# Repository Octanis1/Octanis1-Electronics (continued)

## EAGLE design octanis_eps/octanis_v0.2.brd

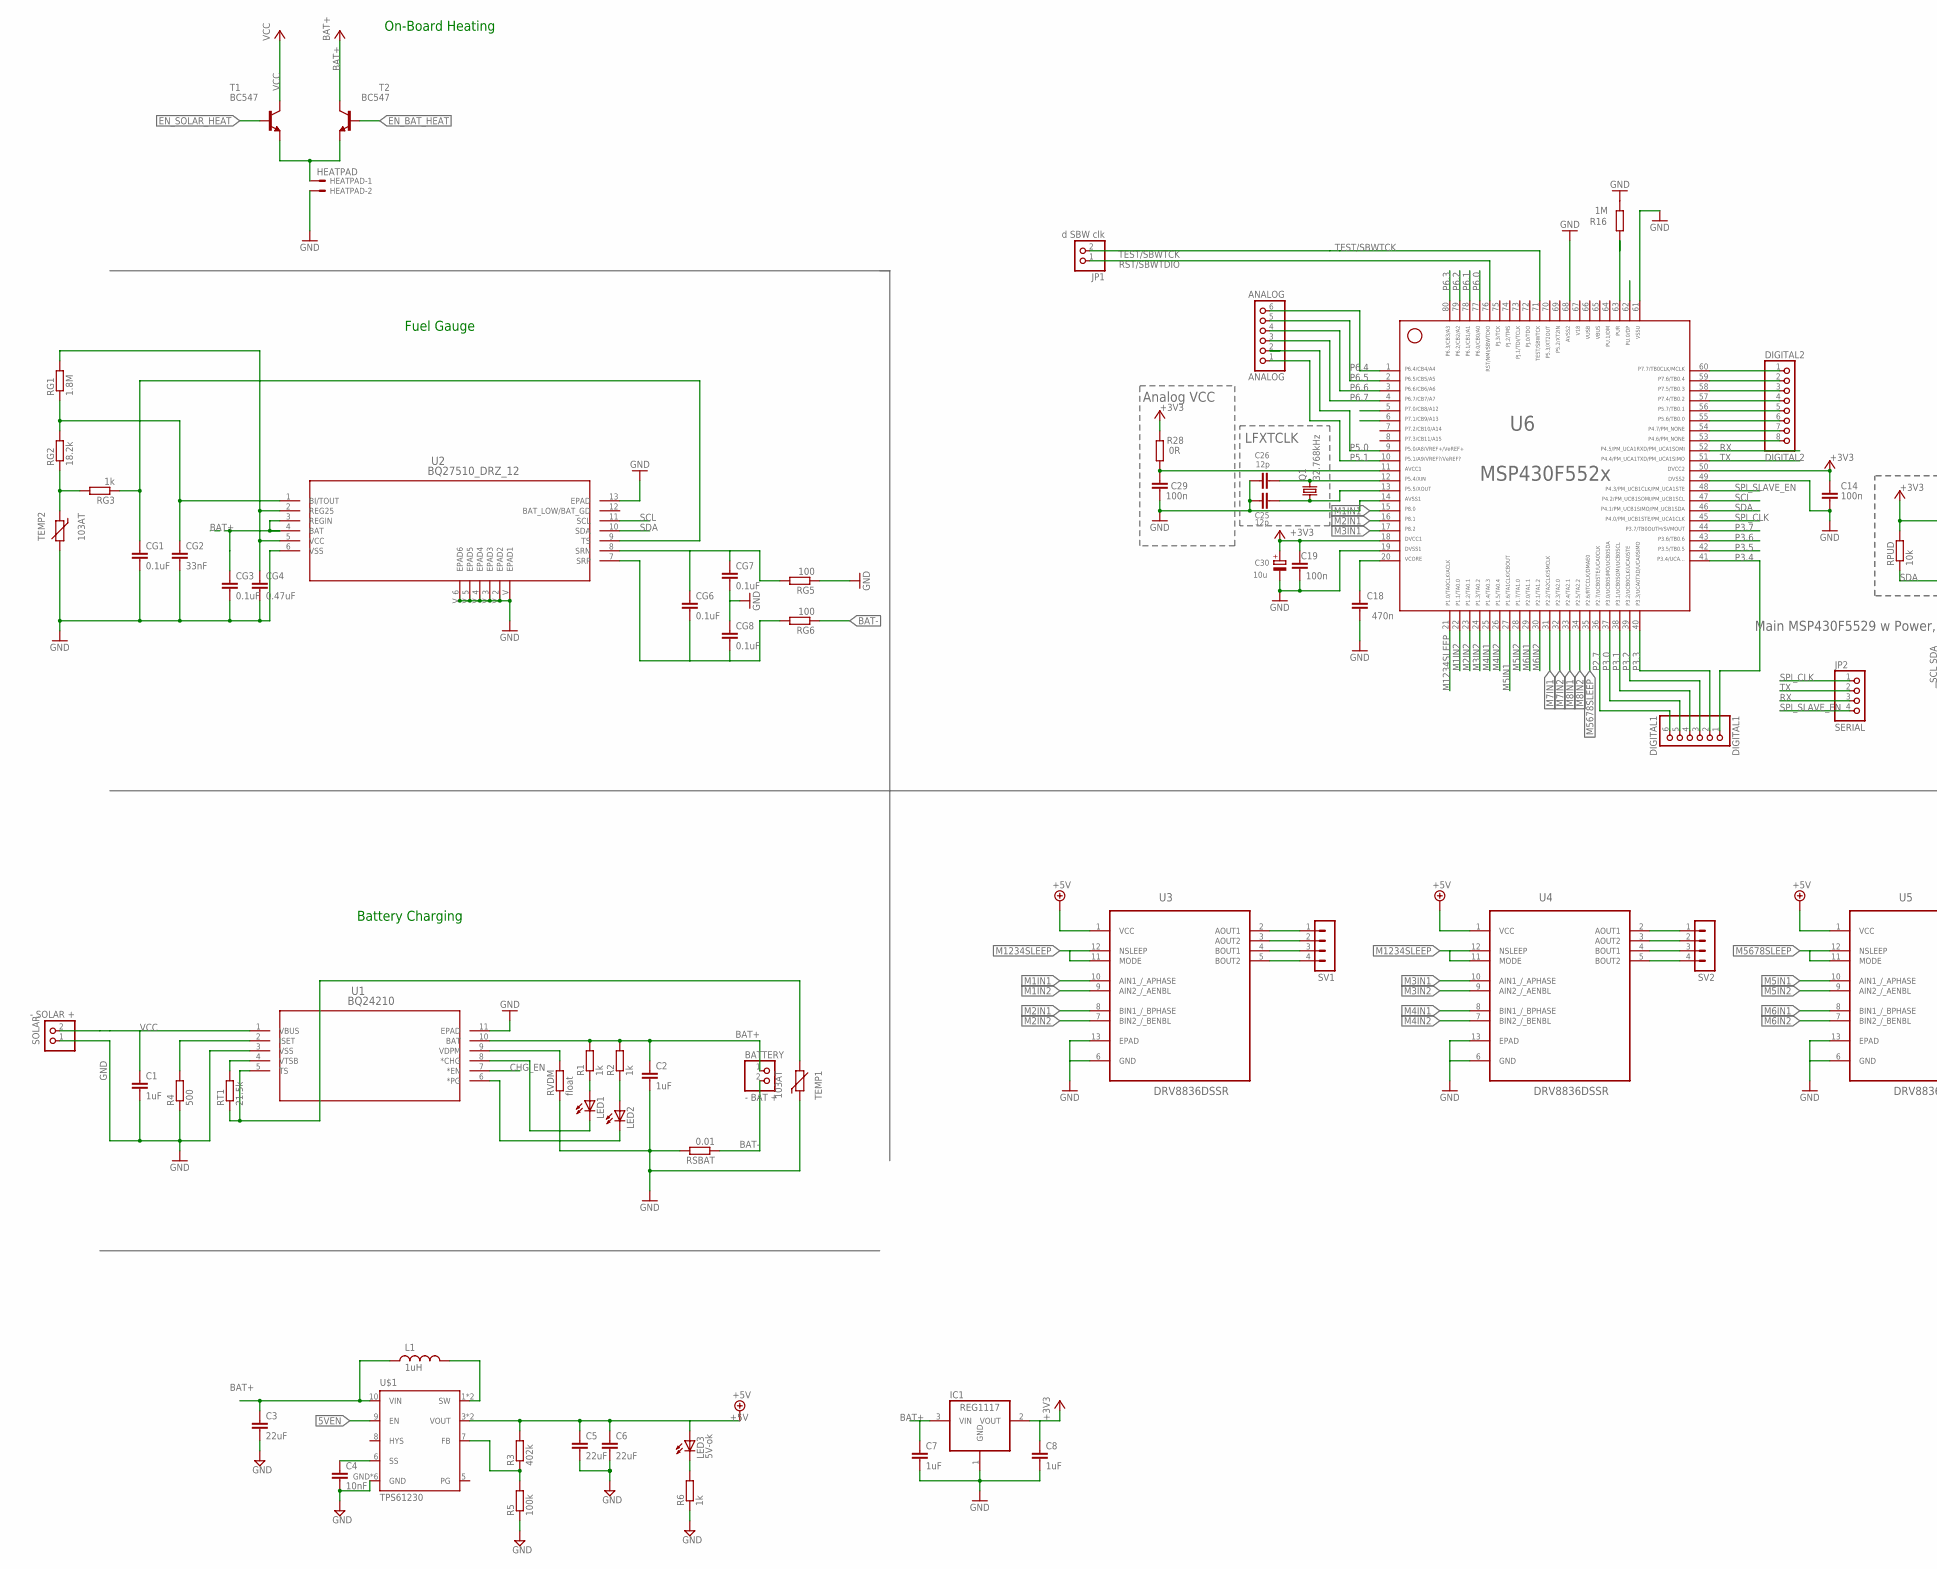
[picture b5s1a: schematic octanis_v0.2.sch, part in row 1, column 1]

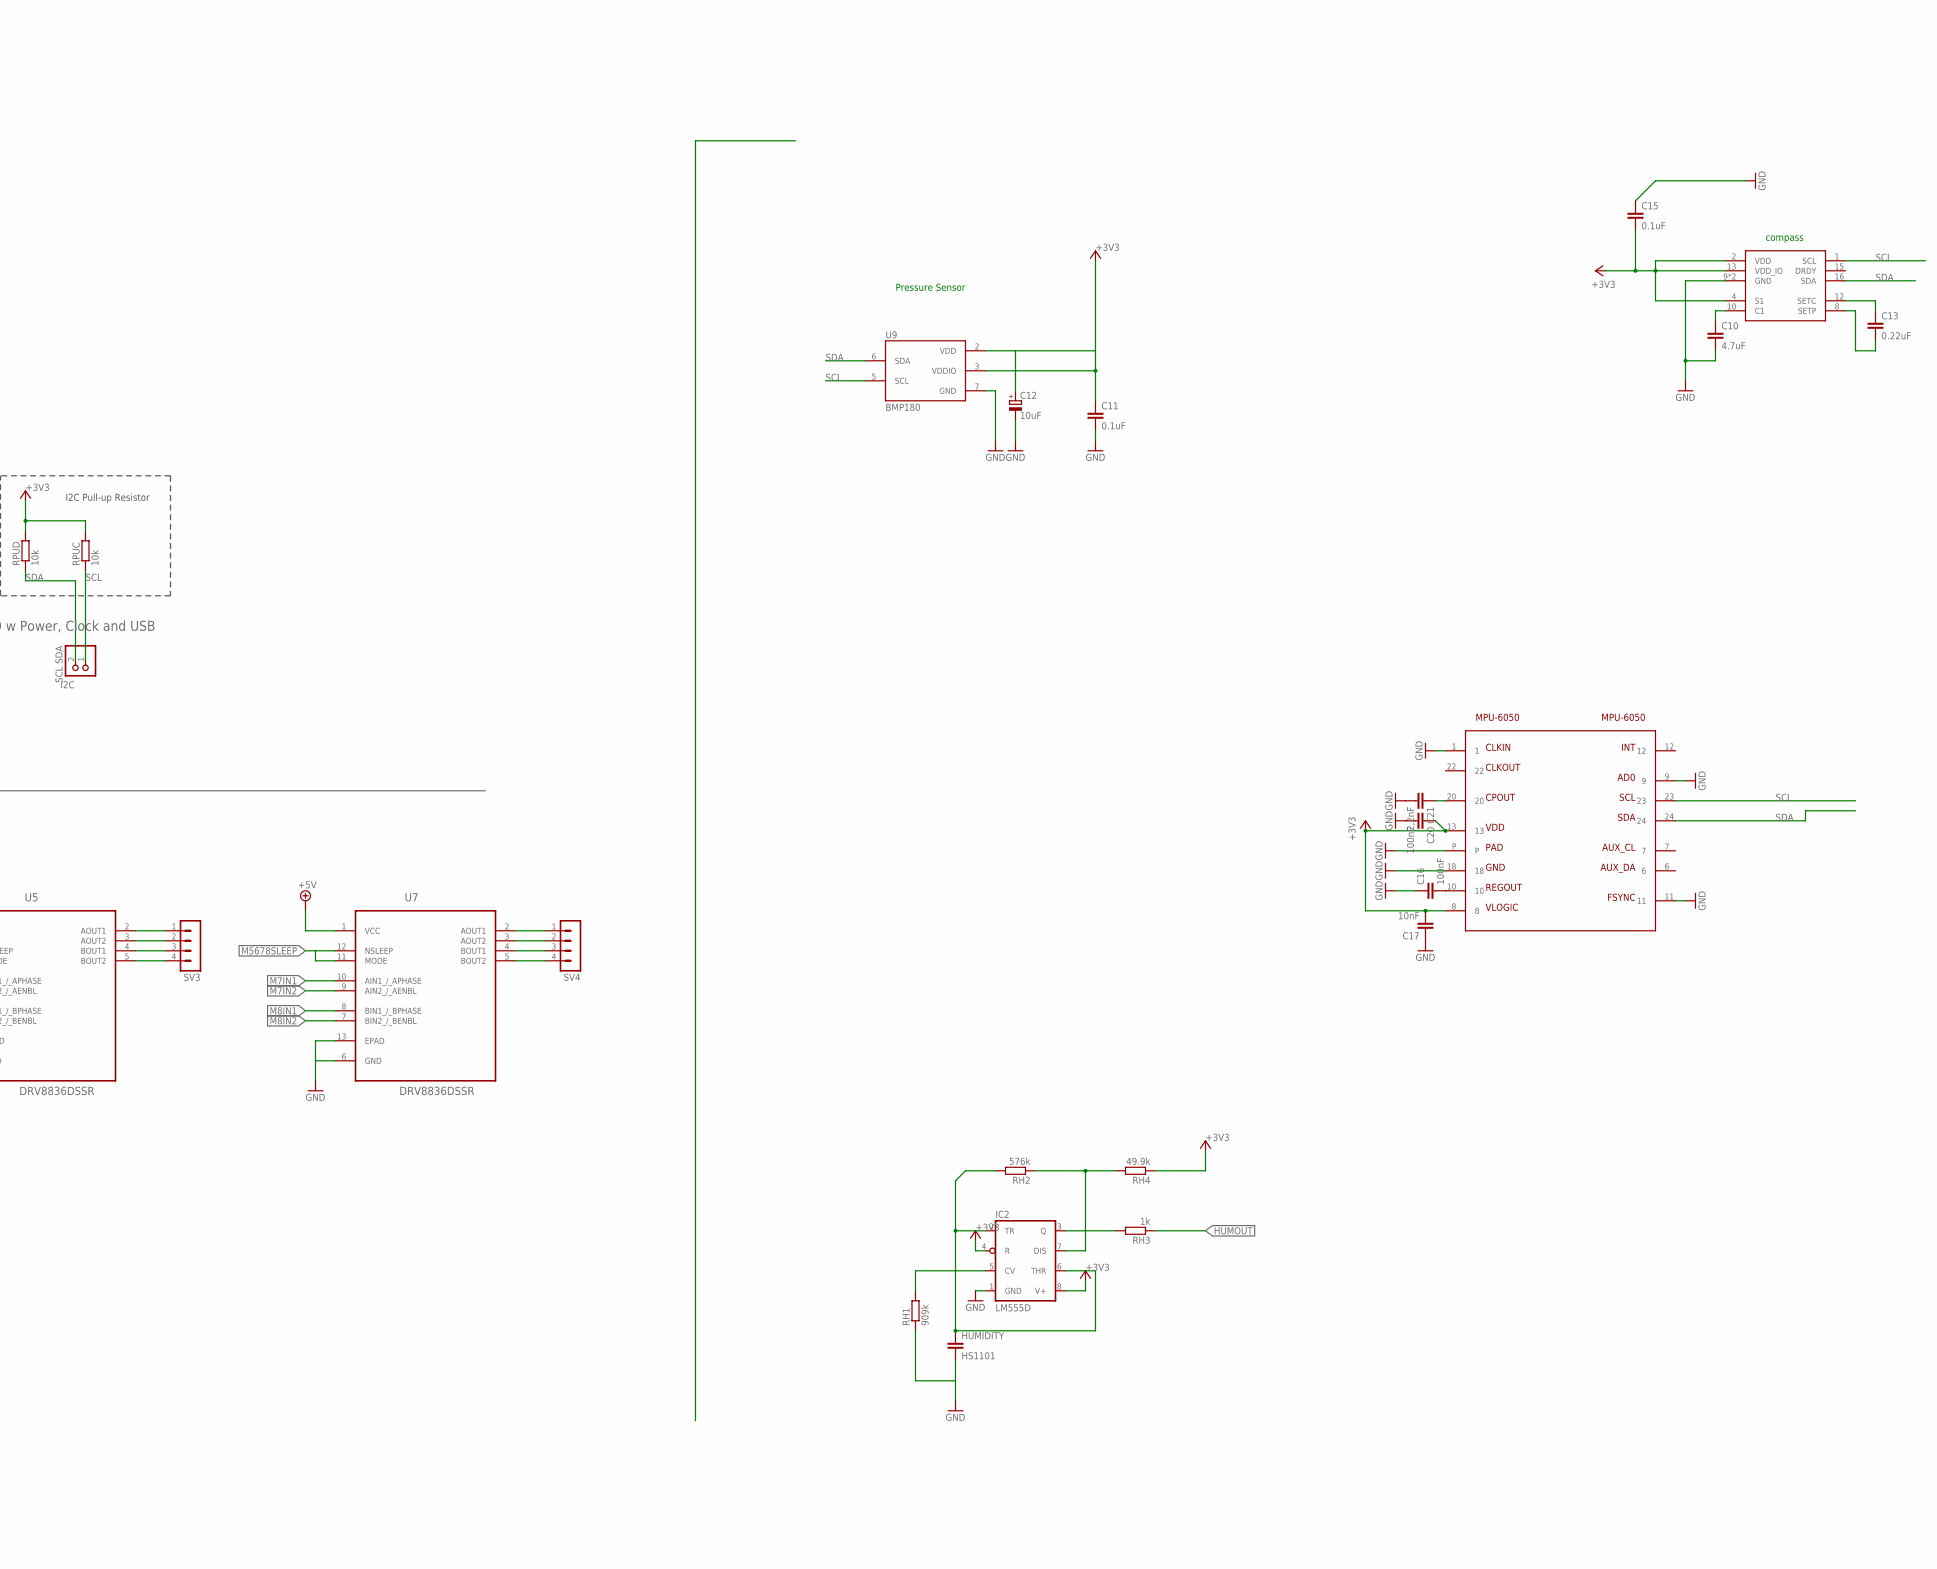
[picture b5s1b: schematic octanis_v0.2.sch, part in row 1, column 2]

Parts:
ANALOG: ANALOG; 1X06
BATTERY: - BAT +; 1X02
C1, C2: 1uF; C1206
C3, C5, C6: 22uF; C0603
C4, C17: 10nF; C0603
C7, C8: 1uF; C0603
C10: 4.7uF; C0603
C11, C15: 0.1uF; C0603
C12: 10uF; A/3216-18R
C13: 0.22uF; C0603
C14, C19, C29: 100n; C0603
C16, C20: 100nF; C0603
C18: 470n; C0603
C21: 2,2nF; C0603
C25, C26: 12p; C0603
C30: 10u; A/3216-18R
CG1, CG3, CG6, CG7, CG8: 0.1uF; C0603
CG2: 33nF; C0603
CG4: 0.47uF; C0603
COMPASS: HMC5883L; LPCC16
DIGITAL1: DIGITAL1; 1X06
DIGITAL2: DIGITAL2; 1X08
HEATPAD: HEATPAD; 22-23-2021
HUMIDITY: HS1101; C025-024X044
I2C: SCL SDA; 1X02
IC1: REG1117; SOT223
IC2: LM555D; SO08
JP1: d SBW clk; 1X02
JP2: SERIAL; 1X04
L1: 1uH; XFL4020
LED1, LED2: LEDCHIP-LED0603; CHIP-LED0603
LED3: 5V-ok; CHIPLED_0603
MPU-6050: MPU-6050; QFN24
Q1: 32.768kHz; FC-12M
R1, R2, R6: 1k; R0603
R3: 402k; R0603
R4: 500; R1206
R5: 100k; R0603
R16: 1M; R0603
R28: 0R; R0603
RG1: 1.8M; R0603
RG2: 18.2k; R0603
RG3: 1k; R0603
RG5, RG6: 100; R0603
RH1: 909k; R0603
RH2: 576k; R0603
RH3: 1k; R0603
RH4: 49.9k; R0603
RPUC: 10k; R0603
RPUD: 10k; R0603
RSBAT: 0.01; R1206
RT1: 21.5k; R1206
RVDM: float; R1206
SOLAR: - SOLAR +; 1X02
SV1, SV2, SV3, SV4: MA04-1
T1, T2: BC547; TO92
TEMP1, TEMP2: 103AT; RS-2,5
U1: BQ24210; DQC10_P84X2P4
U2: BQ27510_DRZ_12; DRZ12_1P95X2P45
U3, U4, U5, U7: DRV8836DSSR; SON50P200X300X80-13N
U6: MSP430F5529IPNR; PN80
U9: BMP180
U$1: TPS61230; DRC-S-PVSON-N11

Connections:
5VEN: U6.6, U$1.9 (EN)
65: U6.65
66: U6.66
67: U6.67
+3V3: C8.1, C11.1, C12.+, C14.1, C15.2, C17.2, C19.2, C20.1, C30.+, COMPASS.2 (VDD), COMPASS.4 (S1), COMPASS.13 (VDD_IO), IC1.2 (VOUT), IC2.4 (R), IC2.8 (V+), MPU-6050.8, MPU-6050.13, R28.2, RH4.1, RPUC.2, RPUD.2, U6.18, U6.50, U9.2 (VDD), U9.3 (VDDIO)
+5V: C5.1, C6.1, LED3.A, R3.2, U3.1 (VCC), U4.1 (VCC), U5.1 (VCC), U7.1 (VCC), U$1.3 (VOUT), U$1.4 (VOUT)
AVCC: C29.1, R28.1, U6.11
BAT+: BATTERY.1, C2.1, C3.1, C7.1, CG3.1, IC1.3 (VIN), L1.P$1 (1), R1.2, R2.2, T2.3 (C), U1.10 (BAT), U2.3 (REGIN), U2.4 (BAT), U$1.10 (VIN)
BAT-: BATTERY.2, RG6.1, RSBAT.1
CHG_EN: U1.7 (*EN), U6.5
EN_BAT_HEAT: T2.2 (B)
EN_SOLAR_HEAT: T1.2 (B)
GND: C1.2, C2.2, C3.2, C4.2, C5.2, C6.2, C7.2, C8.2, C10.2, C11.2, C12.-, C14.2, C15.1, C16.1, C17.1, C18.1, C19.1, C20.2, C21.2, C25.1, C26.1, C29.2, C30.-, CG1.2, CG2.2, CG3.2, CG4.2, CG7.2, CG8.1, COMPASS.9 (GND), COMPASS.11 (GND), HEATPAD.2, HUMIDITY.2, IC1.1 (GND), IC2.1 (GND), MPU-6050.1, MPU-6050.9, MPU-6050.11, MPU-6050.18, MPU-6050.P, R4.1, R5.1, R6.1, R16.1, RG5.1, RH1.1, RSBAT.2, RVDM.1, SOLAR.1, TEMP1.1, TEMP2.2, U1.3 (VSS), U1.11 (EPAD), U2.6 (VSS), U2.13 (EPAD), U2.V (EPAD1), U2.V_2 (EPAD2), U2.V_3 (EPAD3), U2.V_4 (EPAD4), U2.V_5 (EPAD5), U2.V_6 (EPAD6), U3.6 (GND), U3.13 (EPAD), U4.6 (GND), U4.13 (EPAD), U5.6 (GND), U5.13 (EPAD), U6.14, U6.19, U6.49, U6.61, U6.68, U7.6 (GND), U7.13 (EPAD), U9.7 (GND), U$1.GND, U$1.GND@1 (GND), U$1.GND@2 (GND), U$1.GND@3 (GND), U$1.GND@4 (GND), U$1.GND@5 (GND)
HUMOUT: RH3.1
IND: L1.P$2 (2), U$1.1 (SW), U$1.2 (SW)
M1IN1: U3.10 (AIN1_/_APHASE), U6.15
M1IN2: U3.9 (AIN2_/_AENBL), U6.22
M2IN1: U3.8 (BIN1_/_BPHASE), U6.16
M2IN2: U3.7 (BIN2_/_BENBL), U6.23
M3IN1: U4.10 (AIN1_/_APHASE), U6.17
M3IN2: U4.9 (AIN2_/_AENBL), U6.24
M4IN1: U4.8 (BIN1_/_BPHASE), U6.25
M4IN2: U4.7 (BIN2_/_BENBL), U6.26
M5IN1: U5.10 (AIN1_/_APHASE), U6.27
M5IN2: U5.9 (AIN2_/_AENBL), U6.28
M6IN1: U5.8 (BIN1_/_BPHASE), U6.29
M6IN2: U5.7 (BIN2_/_BENBL), U6.30
M7IN1: U6.31, U7.10 (AIN1_/_APHASE)
M7IN2: U6.32, U7.9 (AIN2_/_AENBL)
M8IN1: U6.33, U7.8 (BIN1_/_BPHASE)
M8IN2: U6.34, U7.7 (BIN2_/_BENBL)
M1234SLEEP: U3.11 (MODE), U3.12 (NSLEEP), U4.11 (MODE), U4.12 (NSLEEP), U6.21
M5678SLEEP: U5.11 (MODE), U5.12 (NSLEEP), U6.35, U7.11 (MODE), U7.12 (NSLEEP)
unnamed: CG2.1, RG1.1, RG2.2, U2.1 (BI/TOUT)
unnamed: LED1.A, R1.1
unnamed: LED2.A, R2.1
unnamed: LED1.C, U1.8 (*CHG)
unnamed: LED2.C, U1.6 (*PG)
unnamed: RVDM.2, U1.9 (VDPM)
unnamed: RT1.1, TEMP1.2, U1.5 (TS)
unnamed: RT1.2, U1.4 (VTSB)
unnamed: R4.2, U1.2 (ISET)
unnamed: SV2.1, U4.2 (AOUT1)
unnamed: DIGITAL2.1, U6.60
unnamed: DIGITAL2.2, U6.59
unnamed: C10.1, COMPASS.10 (C1)
unnamed: C16.2, MPU-6050.10
unnamed: C21.1, MPU-6050.20
unnamed: DIGITAL2.3, U6.58
unnamed: DIGITAL2.4, U6.57
unnamed: DIGITAL2.5, U6.56
unnamed: DIGITAL2.6, U6.55
unnamed: DIGITAL2.7, U6.54
unnamed: C13.2, COMPASS.8 (SETP)
unnamed: DIGITAL2.8, U6.53
unnamed: IC2.5 (CV), RH1.2
unnamed: HUMIDITY.1, IC2.2 (TR), IC2.6 (THR), RH2.2
unnamed: IC2.7 (DIS), RH2.1, RH4.2
unnamed: IC2.3 (Q), RH3.2
unnamed: C13.1, COMPASS.12 (SETC)
unnamed: RG2.1, RG3.2, TEMP2.1
unnamed: CG1.1, RG3.1, U2.9 (TS)
unnamed: CG4.1, RG1.2, U2.2 (REG25), U2.5 (VCC)
unnamed: CG6.1, CG7.1, RG5.2, U2.8 (SRN)
unnamed: HEATPAD.1, T1.1 (E), T2.1 (E)
unnamed: CG6.2, CG8.2, RG6.2, U2.7 (SRP)
unnamed: SV2.2, U4.3 (AOUT2)
unnamed: SV2.3, U4.4 (BOUT1)
unnamed: SV2.4, U4.5 (BOUT2)
unnamed: C4.1, U$1.6 (SS)
unnamed: R3.1, R5.2, U$1.7 (FB)
unnamed: LED3.C, R6.2
unnamed: SV3.1, U5.2 (AOUT1)
unnamed: SV3.2, U5.3 (AOUT2)
unnamed: SV3.3, U5.4 (BOUT1)
unnamed: SV3.4, U5.5 (BOUT2)
unnamed: SV1.1, U3.2 (AOUT1)
unnamed: SV1.2, U3.3 (AOUT2)
unnamed: SV1.3, U3.4 (BOUT1)
unnamed: SV1.4, U3.5 (BOUT2)
unnamed: SV4.1, U7.2 (AOUT1)
unnamed: SV4.2, U7.3 (AOUT2)
unnamed: SV4.3, U7.4 (BOUT1)
unnamed: SV4.4, U7.5 (BOUT2)
P2.7: DIGITAL1.6, U6.36
P3.0: DIGITAL1.5, U6.37
P3.1: DIGITAL1.4, U6.38
P3.2: DIGITAL1.3, U6.39
P3.3: DIGITAL1.2, U6.40
P3.4: DIGITAL1.1, U6.41
P3.5: U6.42
P3.6: U6.43
P3.7: U6.44
P5.0: ANALOG.2, U6.9
P5.1: ANALOG.1, U6.10
P5.4/XIN: C26.2, Q1.2, U6.12
P5.5/XOUT: C25.2, Q1.1, U6.13
P6.0: U6.77
P6.1: U6.78
P6.2: U6.79
P6.3: U6.80
P6.4: ANALOG.6, U6.1
P6.5: ANALOG.5, U6.2
P6.6: ANALOG.4, U6.3
P6.7: ANALOG.3, U6.4
PG: U$1.5 (PG)
RST/SBWTDIO: JP1.1, U6.76
RX: JP2.3, U6.52
SCL: COMPASS.1 (SCL), I2C.1, MPU-6050.23, RPUC.1, U2.11 (SCL), U6.47, U9.5 (SCL)
SDA: COMPASS.16 (SDA), I2C.2, MPU-6050.24, RPUD.1, U2.10 (SDA), U6.46, U9.6 (SDA)
SPI_CLK: JP2.1, U6.45
SPI_SLAVE_EN: JP2.4, U6.48
TARGET_DP: U6.62
TARGET_PUR: R16.2, U6.63
TEST/SBWTCK: JP1.2, U6.71
TX: JP2.2, U6.51
VCC: C1.1, SOLAR.2, T1.3 (C), U1.1 (VBUS)
VCORE: C18.2, U6.20

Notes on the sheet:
Battery Charging
Fuel Gauge
LFXTCLK
Main MSP430F5529 w Power, Clock and USB
Analog VCC
I2C Pull-up Resistor
On-Board Heating
Pressure Sensor
compass

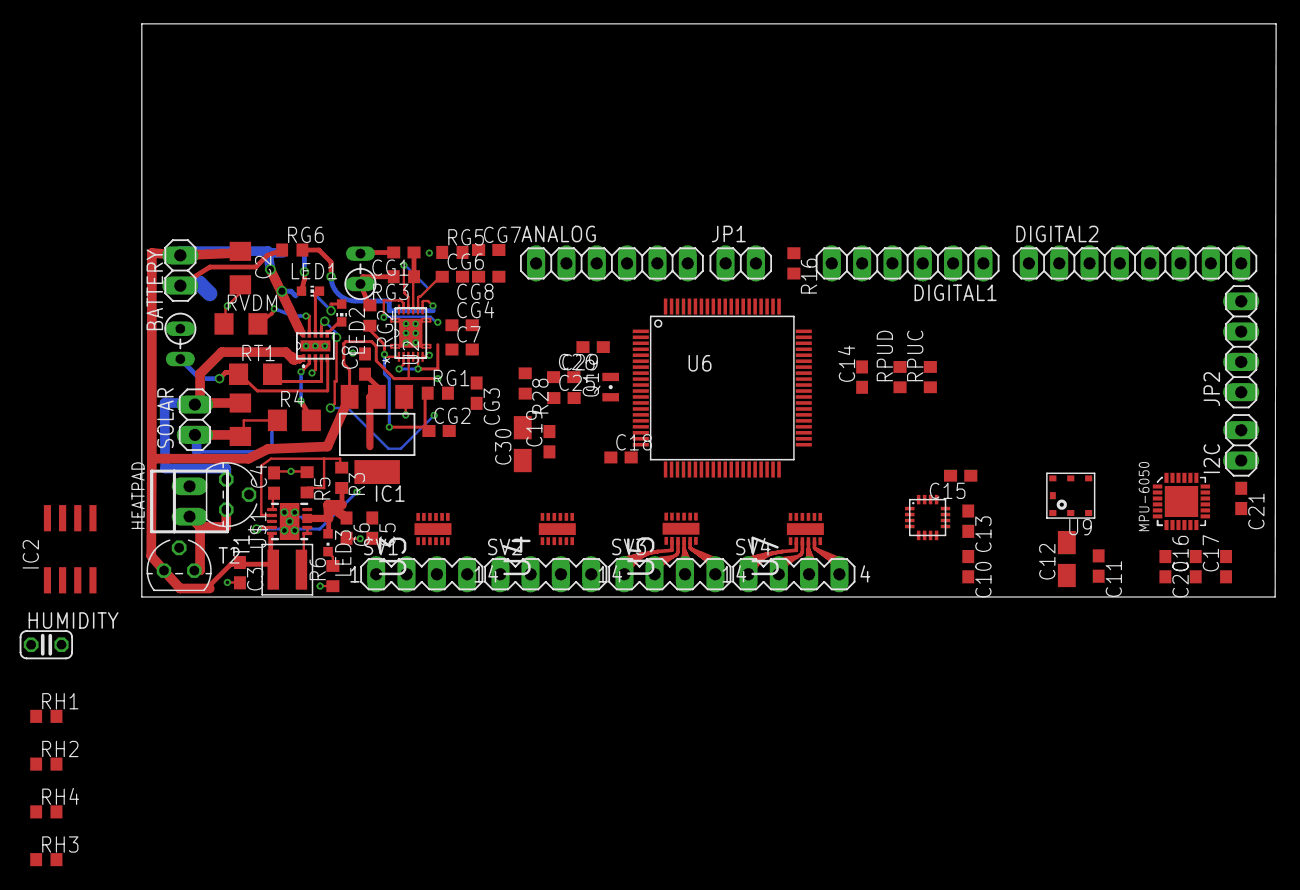
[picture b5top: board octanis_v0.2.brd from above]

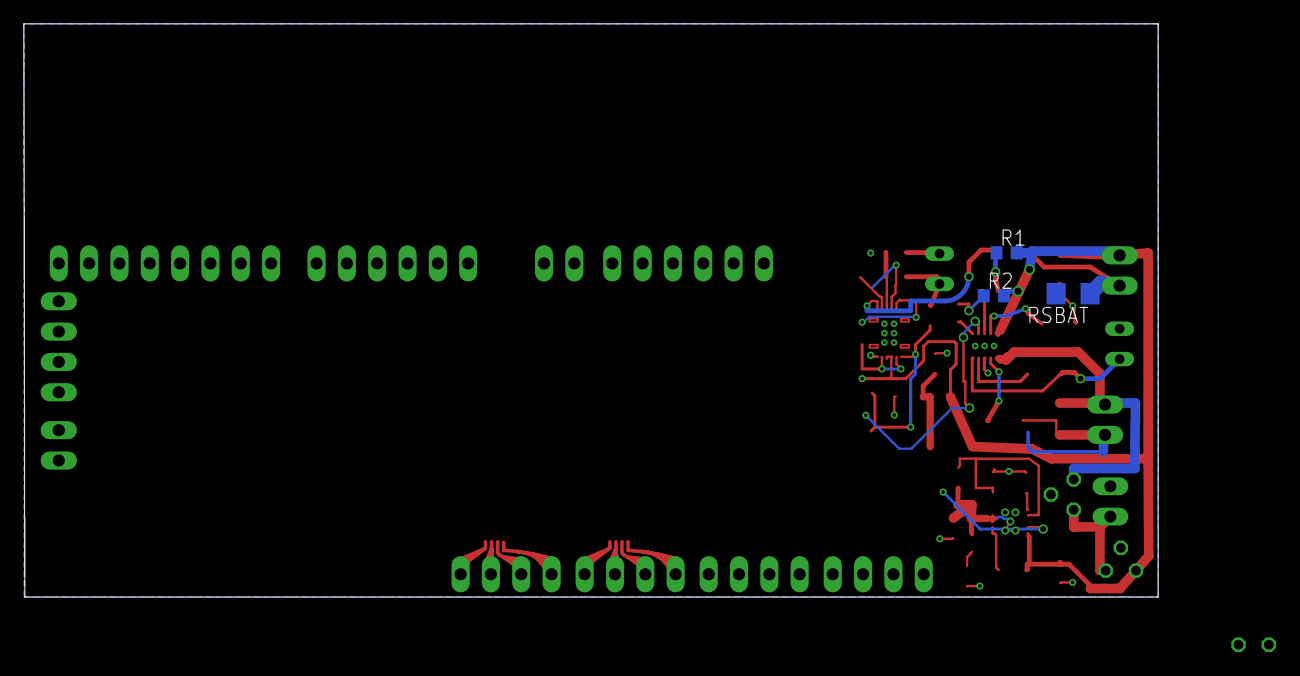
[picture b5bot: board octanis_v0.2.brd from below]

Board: 4 copper layers, 95.0 x 48.0 mm, 89 parts (3 on the bottom side), 103 nets.
